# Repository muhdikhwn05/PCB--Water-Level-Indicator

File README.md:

# PCB--Water-Level-Indicator
A custom PCB design for a water level indicator using BC337 transistors to trigger LED status indicators at 25%, 50%, 75%, 100%, and an alarm state.

> 📹 **Video Demonstration:**
> 

## Hardware Design using KiCAD
**Schematic**

**PCB**

## References & Credits
* **Original Concept:** Core circuit logic inspired by this [YouTube Tutorial](https://www.youtube.com/watch?v=6KDPmU4elMU).
]

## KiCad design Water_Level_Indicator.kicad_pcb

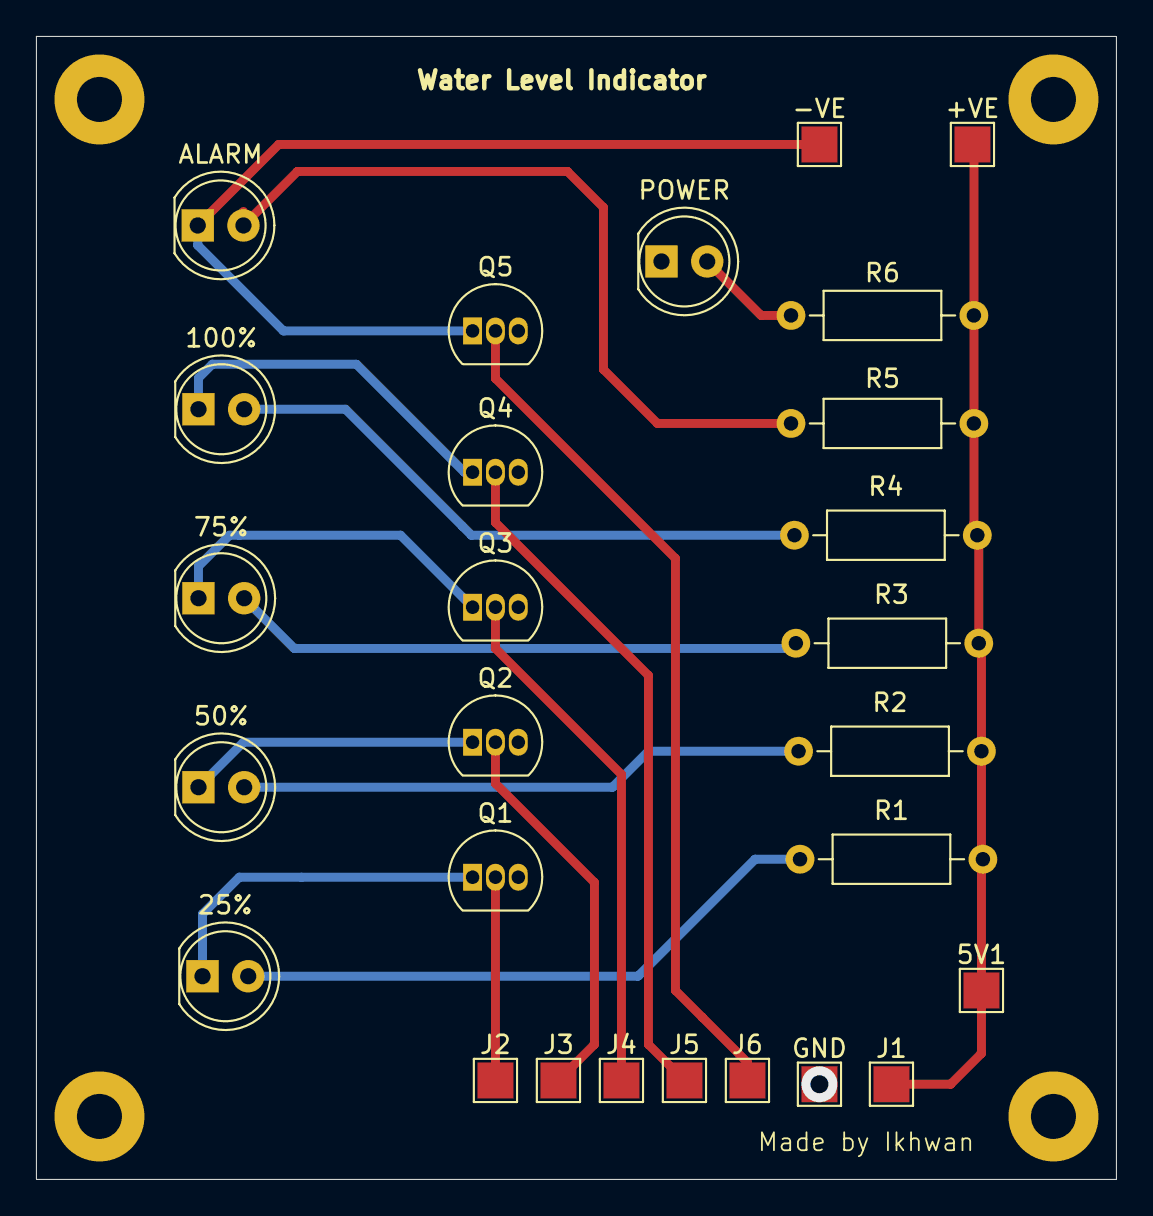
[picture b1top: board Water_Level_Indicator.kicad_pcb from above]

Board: 2 copper layers, 60.0 x 63.5 mm, 27 parts (0 on the bottom side), 18 nets.

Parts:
5V1: TestPoint_Pad_2.0x2.0mm
25%, 50%, 75%, 100%: LED_D5.0mm
+VE: TestPoint_Pad_2.0x2.0mm
-VE: TestPoint_Pad_2.0x2.0mm
ALARM: LED_D5.0mm
GND: TestPoint_Pad_2.0x2.0mm
J1, J2, J3, J4, J5, J6: TestPoint_Pad_2.0x2.0mm
POWER: LED_D5.0mm
Q1, Q2, Q3, Q4, Q5: BC337; TO-92_Inline
R1, R2, R3, R4, R5, R6: 330; R_Axial_DIN0207_L6.3mm_D2.5mm_P10.16mm_Horizontal

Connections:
unnamed: 25%.2 (A), R1.2
unnamed: 25%.1 (K), Q1.1 (C)
unnamed: 50%.2 (A), R2.2
unnamed: 50%.1 (K), Q2.1 (C)
unnamed: 75%.2 (A), R3.2
unnamed: 75%.1 (K), Q3.1 (C)
unnamed: 100%.2 (A), R4.2
unnamed: 100%.1 (K), Q4.1 (C)
unnamed: 5V1.1, +VE.1, J1.1, R1.1, R2.1, R3.1, R4.1, R5.1, R6.2
unnamed: -VE.1, ALARM.1 (K), Q5.1 (C)
unnamed: ALARM.2 (A), R5.2
unnamed: GND.1, POWER.1 (K), Q1.3 (E), Q2.3 (E), Q3.3 (E), Q4.3 (E), Q5.3 (E)
unnamed: J2.1, Q1.2 (B)
unnamed: J3.1, Q2.2 (B)
unnamed: J4.1, Q3.2 (B)
unnamed: J5.1, Q4.2 (B)
unnamed: J6.1, Q5.2 (B)
unnamed: POWER.2 (A), R6.1
